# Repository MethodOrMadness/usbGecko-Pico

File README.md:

# usbGecko-Pico
a USB Gecko clone... for the pi pico

# Why?
Well, the CPLD in the gecko isnt easy to come by, ask me how i know, so im going to attempt to rewrite the Verilog to C code and use it on the pico

# What needs to be done?
Currently, everything
* Translate the Verliog to C
* Adapt the Translated code to run on the pico
* Debug / Test
* Create a writeup / documentation on how to build one

# What can you do to help?
Well, if you know Verilog, that is the main obstacle now

If you have any PCB Design experience, that could also come in handy for when we get a prototype working

If you have any ideas to contribute, open an issue or PR with any information

# Points of failure
After some more research, it seems that a pico *could* be too slow to perform this task, but a faster microcontroller(like a [teensy 4.0][2], clocking in at 600mhz)

# Credits
Streetwalker on [GC-Forever][1] for the OG USB Gecko Clone

[1]: https://www.gc-forever.com/forums/viewtopic.php?f=26&t=3089
[2]: https://www.electronics-lab.com/new-teensy-4-0-fastest-dev-board-powered-arm-cortex-m7/

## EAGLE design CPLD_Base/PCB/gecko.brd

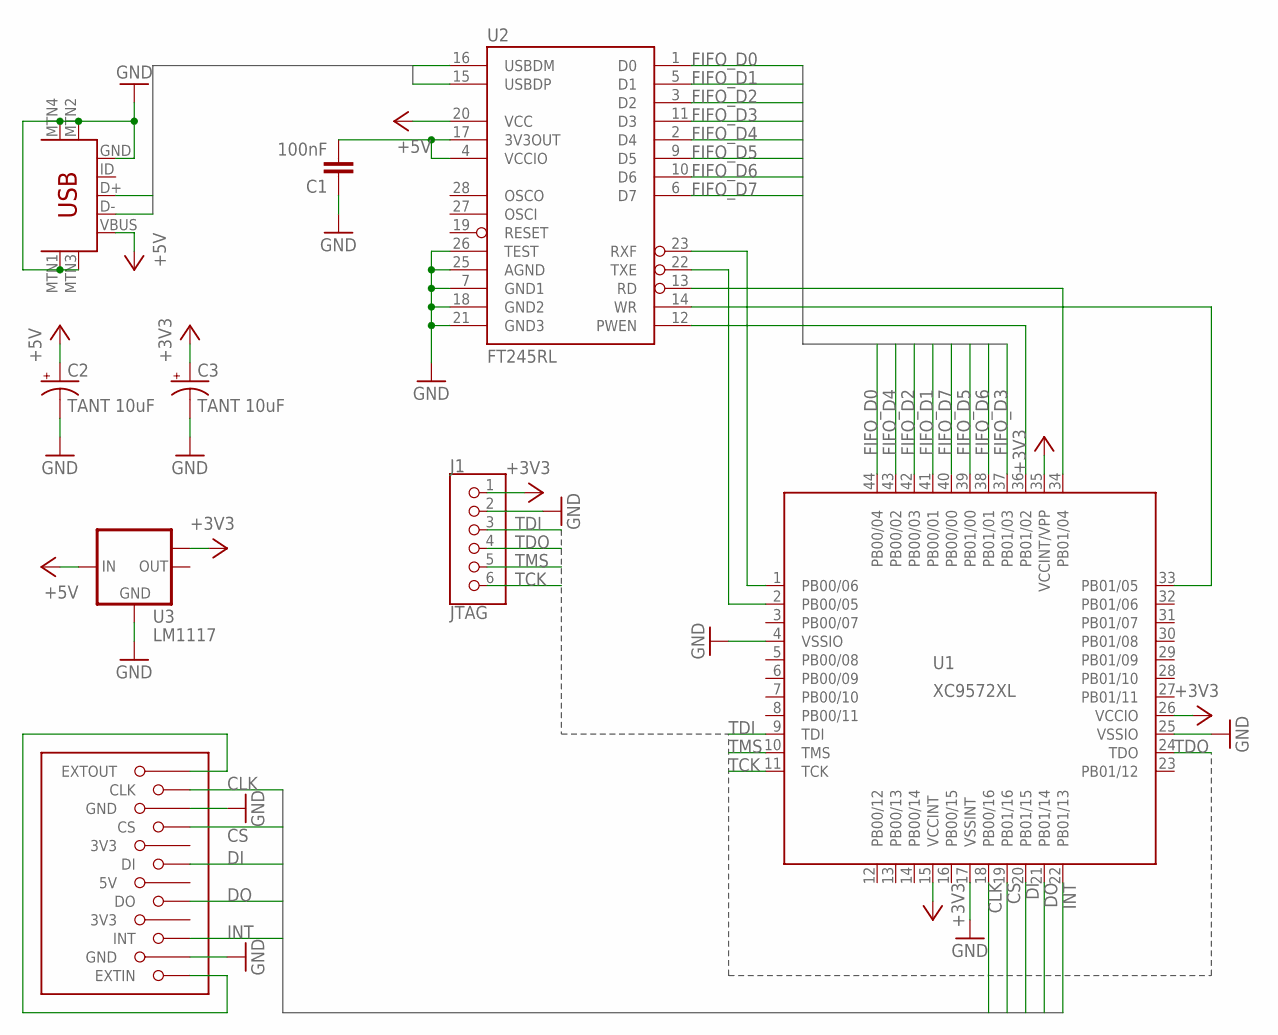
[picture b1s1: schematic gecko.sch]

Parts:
C1: 100nF; C0603
C2, C3: TANT 10uF; EIA3216-KIT
J1: JTAG; WIRE_6
J2: USB-MINIB-5PIN; USB-MINIB
J3: GC_MEMCARD
U1: XC9572XL; SQFP-S-10X10-44
U2: FT245RL; SSOP28DB
U3: LM1117; SOT223

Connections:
+3V3: C3.A (+), J1.1, U1.15 (VCCINT), U1.26 (VCCIO), U1.35 (VCCINT/VPP), U3.TAB (OUT1)
+5V: C2.A (+), J2.VBUS, U2.20 (VCC), U3.3 (IN)
CLK: J3.11 (CLK), U1.18 (PB00/16)
CS: J3.9 (CS), U1.19 (PB01/16)
DI: J3.7 (DI), U1.20 (PB01/15)
DO: J3.5 (DO), U1.21 (PB01/14)
FIFO_D0: U1.44 (PB00/04), U2.1 (D0)
FIFO_D1: U1.41 (PB00/01), U2.5 (D1)
FIFO_D2: U1.42 (PB00/03), U2.3 (D2)
FIFO_D3: U1.37 (PB01/03), U2.11 (D3)
FIFO_D4: U1.43 (PB00/02), U2.2 (D4)
FIFO_D5: U1.39 (PB01/00), U2.9 (D5)
FIFO_D6: U1.38 (PB01/01), U2.10 (D6)
FIFO_D7: U1.40 (PB00/00), U2.6 (D7)
GND: C1.1, C2.C (-), C3.C (-), J1.2, J2.GND, J2.MTN1 (MTN2), J2.MTN2 (MTN3), J2.MTN3 (MTN1), J2.MTN4, J3.2 (GND), J3.10 (GND), U1.4 (VSSIO), U1.17 (VSSINT), U1.25 (VSSIO), U2.7 (GND1), U2.18 (GND2), U2.21 (GND3), U2.25 (AGND), U2.26 (TEST), U3.1 (GND)
INT: J3.3 (INT), U1.22 (PB01/13)
unnamed: C1.2, U2.4 (VCCIO), U2.17 (3V3OUT)
unnamed: U1.36 (PB01/02), U2.12 (PWEN)
unnamed: U1.33 (PB01/05), U2.14 (WR)
unnamed: U1.34 (PB01/04), U2.13 (RD)
unnamed: U1.1 (PB00/06), U2.23 (RXF)
unnamed: U1.2 (PB00/05), U2.22 (TXE)
unnamed: J3.1 (EXTIN), J3.12 (EXTOUT)
TCK: J1.6, U1.11 (TCK)
TDI: J1.3, U1.9 (TDI)
TDO: J1.4, U1.24 (TDO)
TMS: J1.5, U1.10 (TMS)
USB_D+: J2.D+, U2.15 (USBDP)
USB_D-: J2.D-, U2.16 (USBDM)

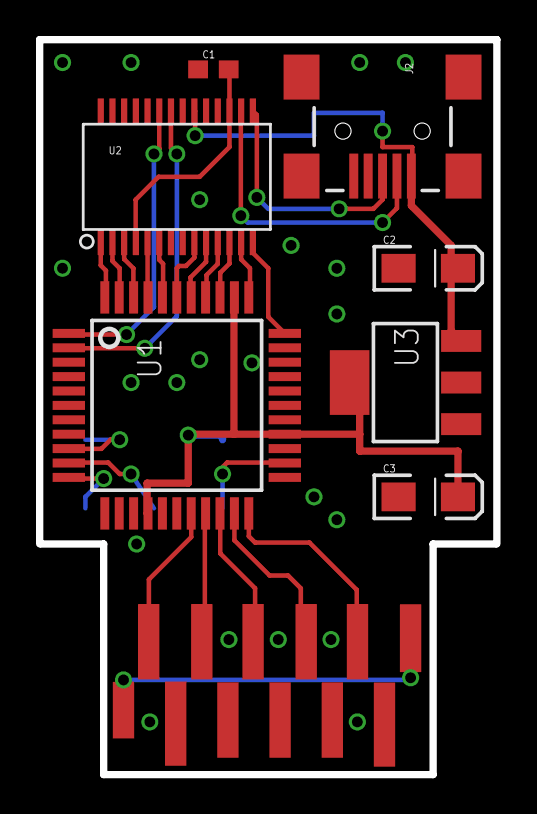
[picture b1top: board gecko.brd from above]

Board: 2 copper layers, 25.4 x 40.8 mm, 9 parts (1 on the bottom side), 29 nets.

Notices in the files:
parts and their libraries:
SparkFun-Capacitors: Licensing: Creative Commons ShareAlike 4.0 International - https://creativecommons.org/licenses/by-sa/4.0
